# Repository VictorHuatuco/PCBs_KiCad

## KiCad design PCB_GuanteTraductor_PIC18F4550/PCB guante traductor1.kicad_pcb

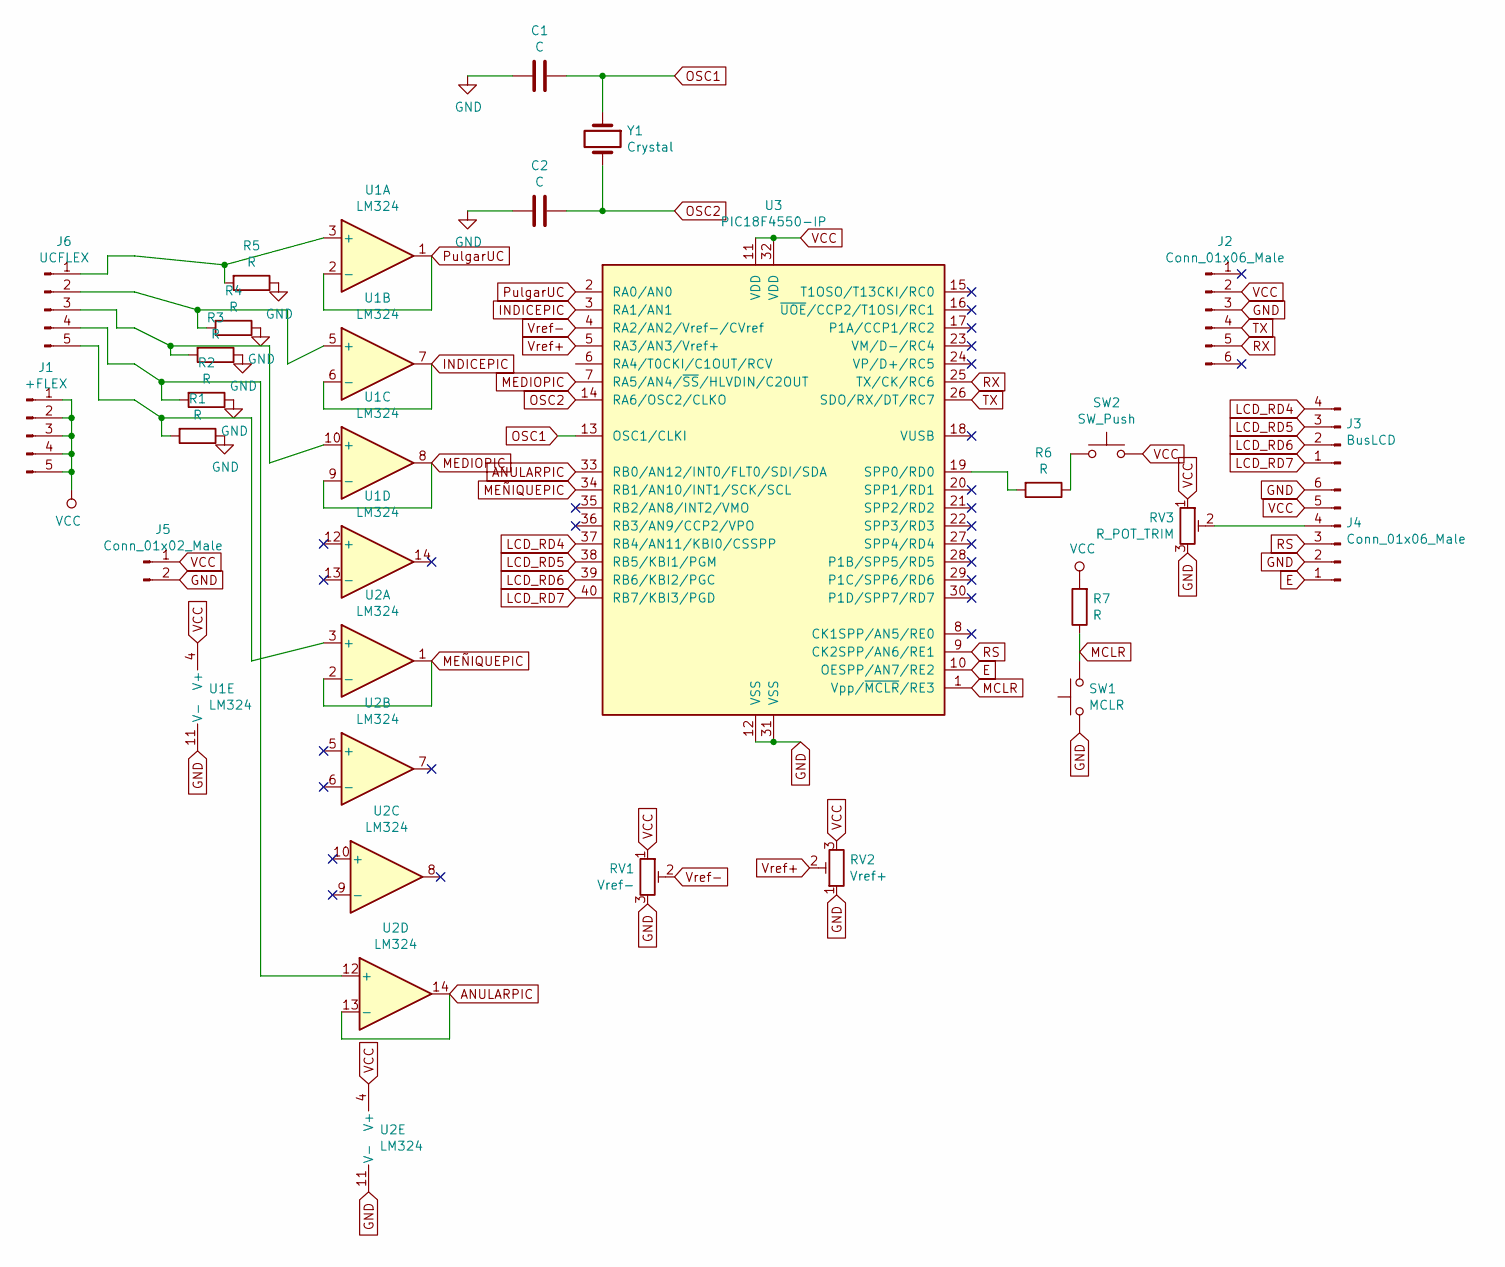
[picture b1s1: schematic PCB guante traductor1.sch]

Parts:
C1, C2: C; C_Disc_D3.0mm_W2.0mm_P2.50mm
J1: +FLEX; PinHeader_1x05_P2.54mm_Vertical
J2, J4: Conn_01x06_Male; PinHeader_1x06_P2.54mm_Vertical
J3: BusLCD; PinHeader_1x04_P2.54mm_Vertical
J5: Conn_01x02_Male; PinHeader_1x02_P2.54mm_Vertical
J6: UCFLEX; PinHeader_1x05_P2.54mm_Vertical
R1, R2, R3, R4, R5, R6, R7: R; R_Axial_DIN0204_L3.6mm_D1.6mm_P7.62mm_Horizontal
RV1: Vref-; Potentiometer_Bourns_3299Y_Vertical
RV2: Vref+; Potentiometer_Bourns_3299Y_Vertical
RV3: R_POT_TRIM; Potentiometer_Bourns_3299Y_Vertical
SW1: MCLR; PinHeader_1x02_P2.54mm_Vertical
SW2: SW_Push; PinHeader_1x02_P2.54mm_Vertical
U1, U2: LM324; DIP-14_W10.16mm
U3: PIC18F4550-IP; DIP-40_W15.24mm
Y1: Crystal; Crystal_HC49-4H_Vertical

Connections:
ANULARPIC: U2.13 (-), U2.14, U3.33 (RB0/AN12/INT0/FLT0/SDI/SDA)
E: J4.1, U3.10 (OESPP/AN7/RE2)
GND: C1.2, C2.2, J2.3, J4.2, J4.6, J5.2, R1.1, R2.1, R3.1, R4.1, R5.1, RV1.3, RV2.1, RV3.3, SW1.1, U1.11 (V-), U2.11 (V-), U3.12 (VSS), U3.31 (VSS)
INDICEPIC: U1.6 (-), U1.7, U3.3 (RA1/AN1)
LCD_RD4: J3.4, U3.37 (RB4/AN11/KBI0/CSSPP)
LCD_RD5: J3.3, U3.38 (RB5/KBI1/PGM)
LCD_RD6: J3.2, U3.39 (RB6/KBI2/PGC)
LCD_RD7: J3.1, U3.40 (RB7/KBI3/PGD)
MCLR: R7.1, SW1.2, U3.1 (Vpp/~MCLR~/RE3)
MEDIOPIC: U1.8, U1.9 (-), U3.7 (RA5/AN4/~SS~/HLVDIN/C2OUT)
MEÑIQUEPIC: U2.1, U2.2 (-), U3.34 (RB1/AN10/INT1/SCK/SCL)
unnamed: J4.4, RV3.2
unnamed: J6.1, R5.2, U1.3 (+)
unnamed: J6.2, R4.2, U1.5 (+)
unnamed: J6.3, R3.2, U1.10 (+)
unnamed: J6.4, R2.2, U2.12 (+)
unnamed: J6.5, R1.2, U2.3 (+)
unnamed: R6.1, SW2.1
unnamed: R6.2, U3.19 (SPP0/RD0)
OSC1: C1.1, U3.13 (OSC1/CLKI), Y1.1
OSC2: C2.1, U3.14 (RA6/OSC2/CLKO), Y1.2
PulgarUC: U1.1, U1.2 (-), U3.2 (RA0/AN0)
RS: J4.3, U3.9 (CK2SPP/AN6/RE1)
RX: J2.5, U3.25 (TX/CK/RC6)
TX: J2.4, U3.26 (SDO/RX/DT/RC7)
VCC: J1.1, J1.2, J1.3, J1.4, J1.5, J2.2, J4.5, J5.1, R7.2, RV1.1, RV2.3, RV3.1, SW2.2, U1.4 (V+), U2.4 (V+), U3.11 (VDD), U3.32 (VDD)
Vref+: RV2.2, U3.5 (RA3/AN3/Vref+)
Vref-: RV1.2, U3.4 (RA2/AN2/Vref-/CVref)

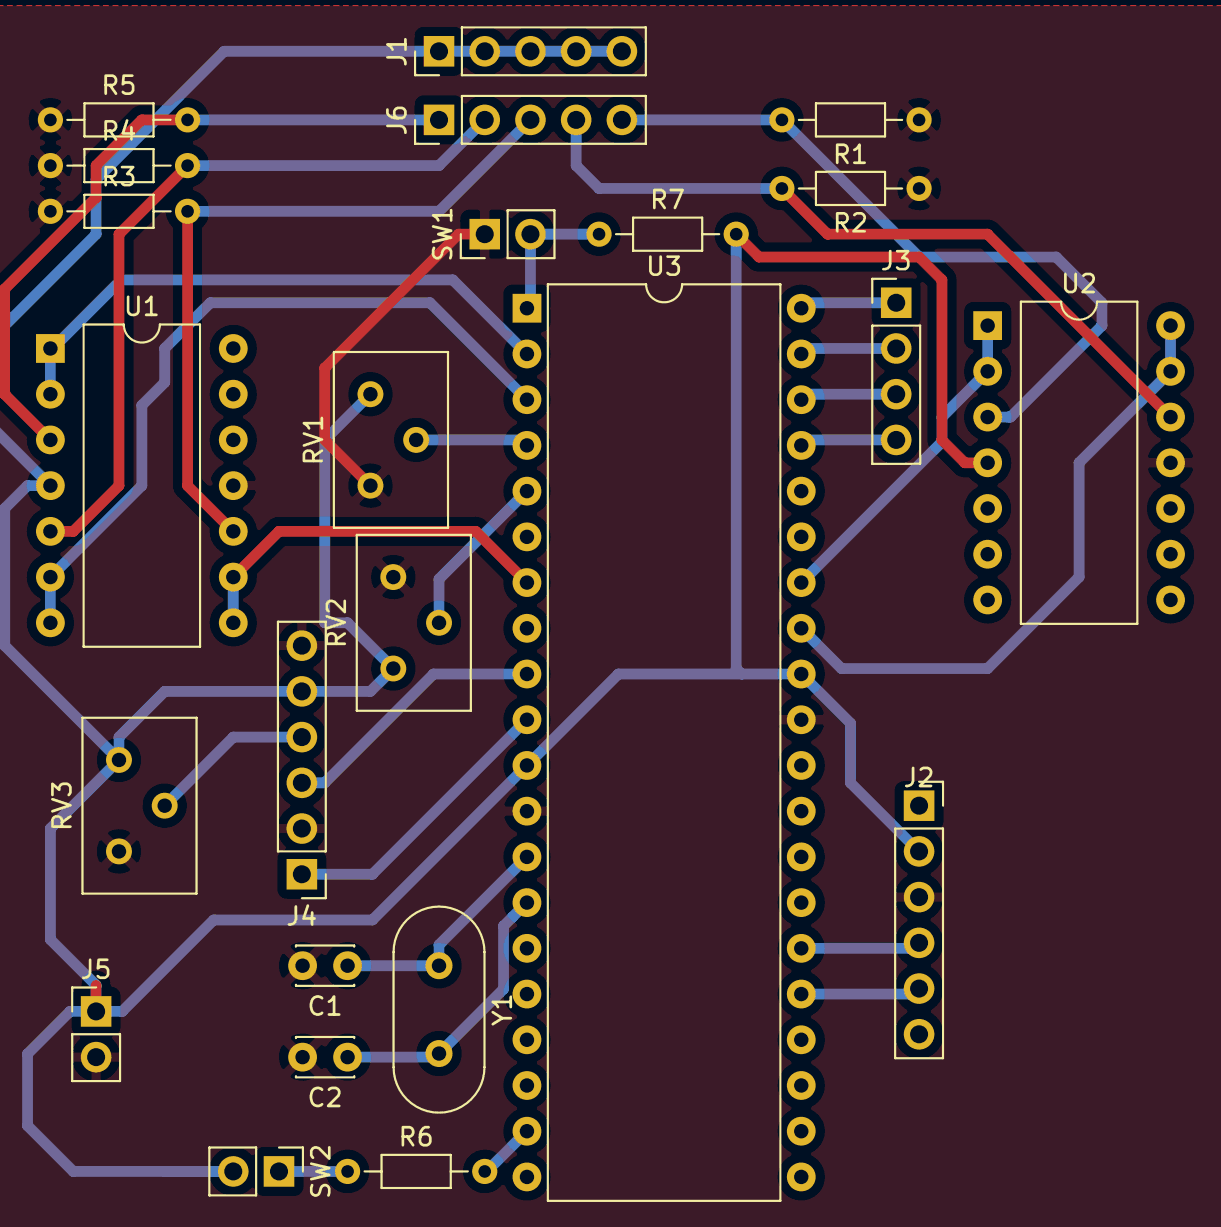
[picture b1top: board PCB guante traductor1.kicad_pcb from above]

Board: 2 copper layers, 24 parts (0 on the bottom side), 28 nets.
